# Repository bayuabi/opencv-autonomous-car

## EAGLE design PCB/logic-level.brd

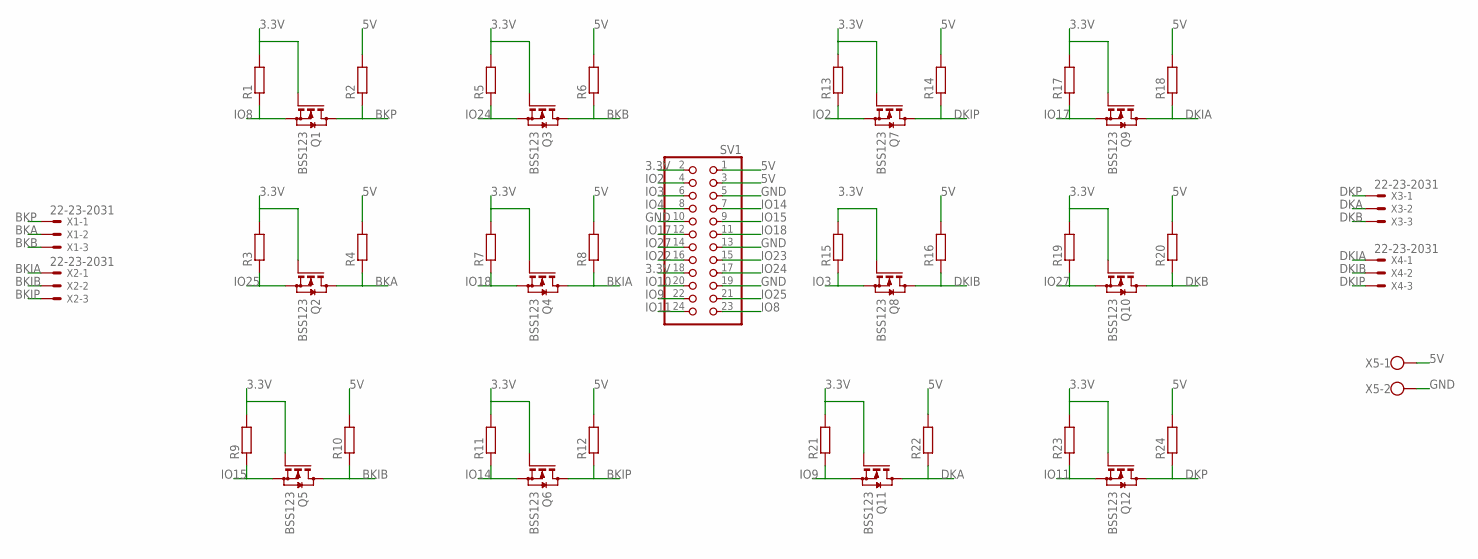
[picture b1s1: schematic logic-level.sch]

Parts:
Q1, Q2, Q3, Q4, Q5, Q6, Q7, Q8, Q9, Q10, Q11, Q12: BSS123; SOT23
R1, R2, R3, R4, R5, R6, R7, R8, R9, R10, R11, R12, R13, R14, R15, R16, R17, R18, R19, R20, R21, R22, R23, R24: R-EU_M1206; M1206
SV1: PINHD-2X12; 2X12
X1, X2, X3, X4: 22-23-2031
X5: W237-102

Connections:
3.3V: Q1.1 (G), Q2.1 (G), Q3.1 (G), Q4.1 (G), Q5.1 (G), Q6.1 (G), Q7.1 (G), Q8.1 (G), Q9.1 (G), Q10.1 (G), Q11.1 (G), Q12.1 (G), R1.2, R3.2, R5.2, R7.2, R9.2, R11.2, R13.2, R15.2, R17.2, R19.2, R21.2, R23.2, SV1.2, SV1.18
5V: R2.2, R4.2, R6.2, R8.2, R10.2, R12.2, R14.2, R16.2, R18.2, R20.2, R22.2, R24.2, SV1.1, SV1.3, X5.1
BKA: Q2.3 (D), R4.1, X1.2
BKB: Q3.3 (D), R6.1, X1.3
BKIA: Q4.3 (D), R8.1, X2.1
BKIB: Q5.3 (D), R10.1, X2.2
BKIP: Q6.3 (D), R12.1, X2.3
BKP: Q1.3 (D), R2.1, X1.1
DKA: Q11.3 (D), R22.1, X3.2
DKB: Q10.3 (D), R20.1, X3.3
DKIA: Q9.3 (D), R18.1, X4.1
DKIB: Q8.3 (D), R16.1, X4.2
DKIP: Q7.3 (D), R14.1, X4.3
DKP: Q12.3 (D), R24.1, X3.1
GND: SV1.5, SV1.10, SV1.13, SV1.19, X5.2
IO2: Q7.2 (S), R13.1, SV1.4
IO3: Q8.2 (S), R15.1, SV1.6
IO4: SV1.8
IO8: Q1.2 (S), R1.1, SV1.23
IO9: Q11.2 (S), R21.1, SV1.22
IO10: SV1.20
IO11: Q12.2 (S), R23.1, SV1.24
IO14: Q6.2 (S), R11.1, SV1.7
IO15: Q5.2 (S), R9.1, SV1.9
IO17: Q9.2 (S), R17.1, SV1.12
IO18: Q4.2 (S), R7.1, SV1.11
IO22: SV1.16
IO23: SV1.15
IO24: Q3.2 (S), R5.1, SV1.17
IO25: Q2.2 (S), R3.1, SV1.21
IO27: Q10.2 (S), R19.1, SV1.14

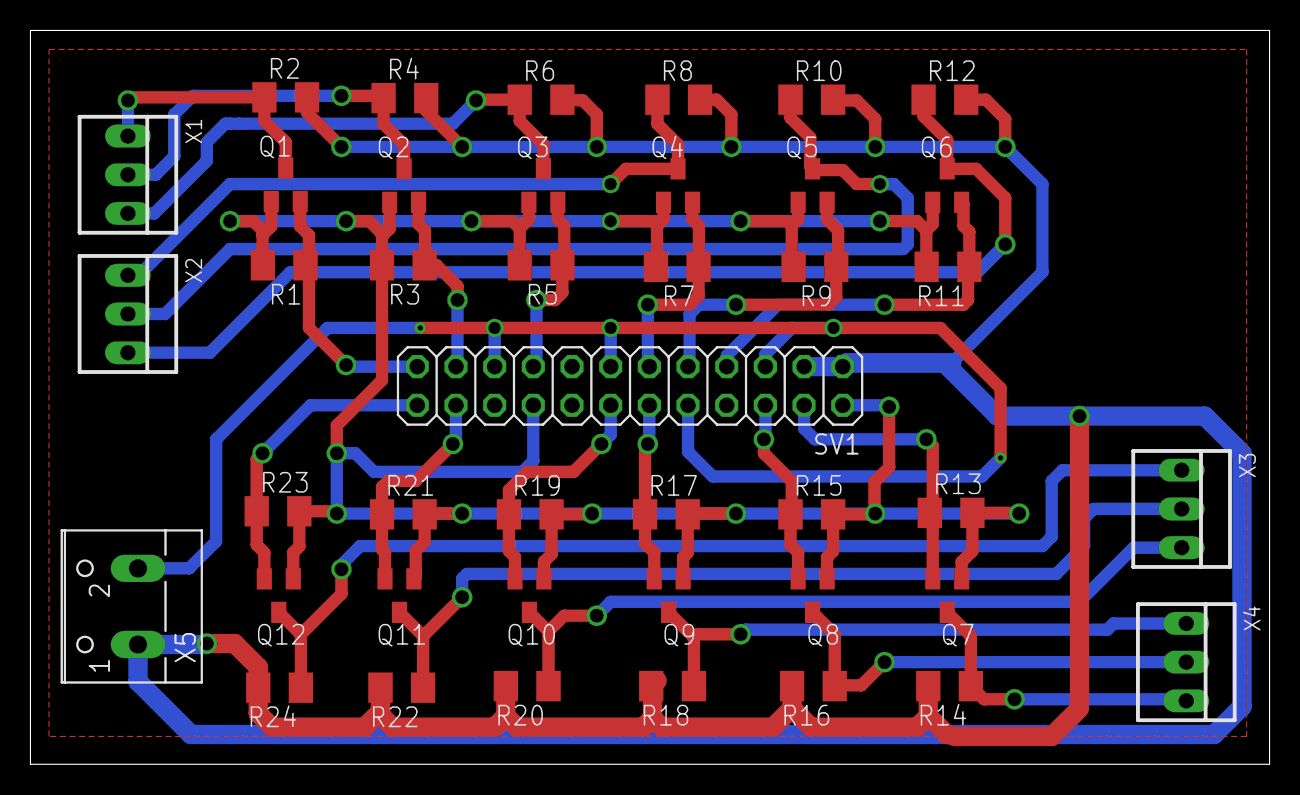
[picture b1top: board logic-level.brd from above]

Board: 2 copper layers, 81.4 x 48.2 mm, 42 parts (0 on the bottom side), 27 nets.

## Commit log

2019-04-13 first commit ever
